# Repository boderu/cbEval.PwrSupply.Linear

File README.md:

# cbEval.PwrSupply.Linear

Evaluation-Board - basierend auf dem modularen Gehäuse von Camdenboss. Stromversorgung mit Linearreglern.

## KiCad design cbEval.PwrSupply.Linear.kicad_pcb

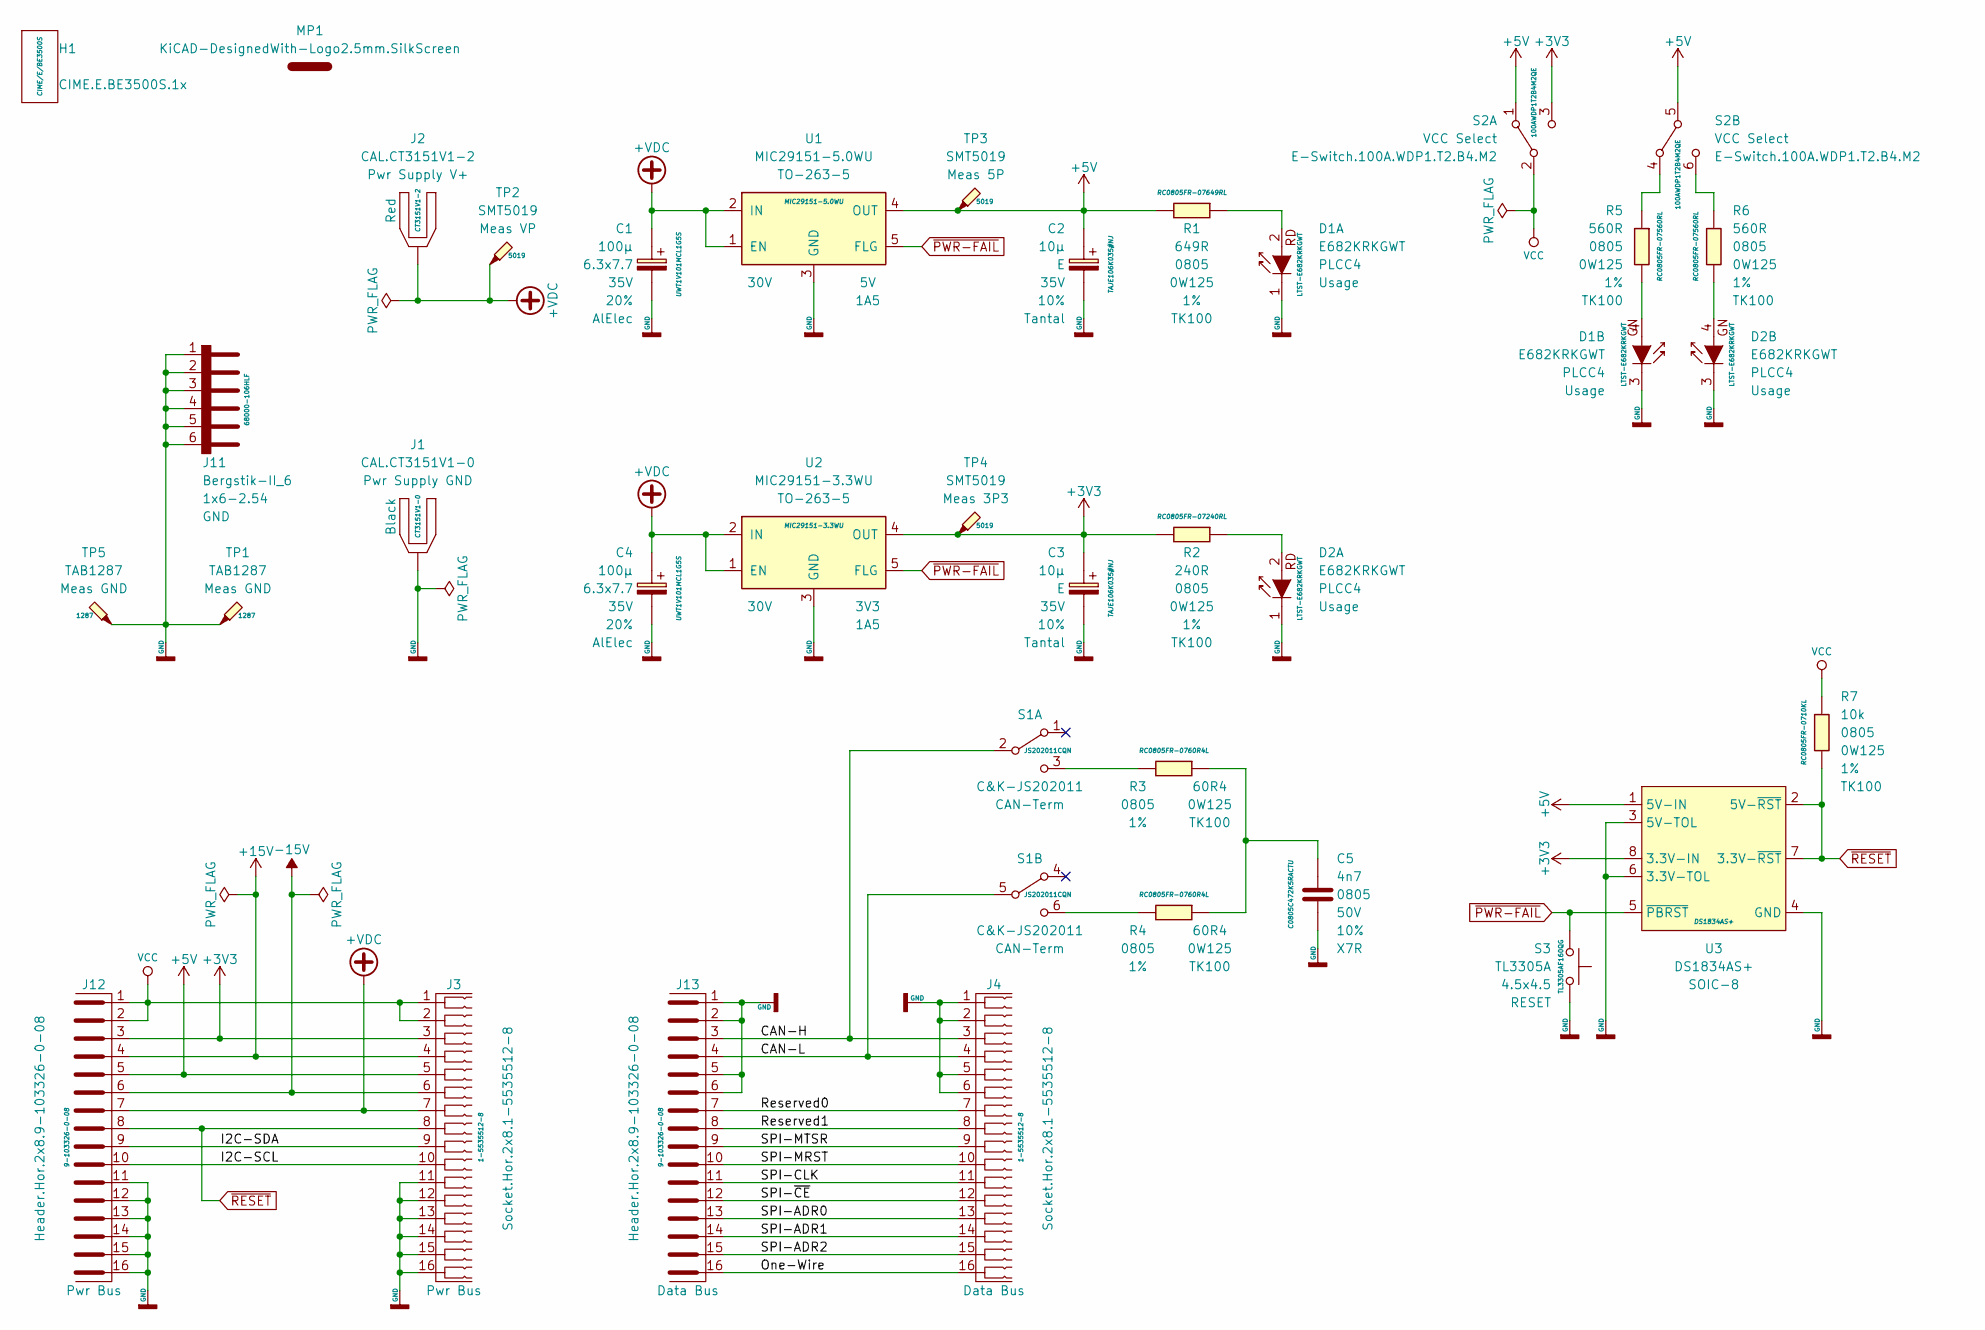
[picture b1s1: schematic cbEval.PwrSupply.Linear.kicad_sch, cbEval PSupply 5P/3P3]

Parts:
C1, C4: 100µ; CP_Elec_6.3x7.7; Voltage 35V; Tolerance 20%
C2, C3: 10µ; CP_EIA-7360-38_Kemet-E; Voltage 35V; Tolerance 10%
C5: 4n7; C_0805_2012Metric; Voltage 50V; Tolerance 10%
D1, D2: E682KRKGWT; LED_Avago_PLCC4_3.2x2.8mm_CW
H1: CIME.E.BE3500S.1x; Camdenboss.CIME.E.BE3500S.1x
J1: CAL.CT3151V1-0; CAL.CT3151V1
J2: CAL.CT3151V1-2; CAL.CT3151V1
J3, J4: Socket.Hor.2x8.1-5535512-8; Socket.Hor.2x5.6-5535512-4
J11: Bergstik-II_6; PinHeader_1x06_P2.54mm_Vertical
J12, J13: Header.Hor.2x8.9-103326-0-08; PinHeader_2x08_P2.54mm_Horizontal
MP1: KiCAD-DesignedWith-Logo2.5mm.SilkScreen; KiCad-Logo2_5mm_SilkScreen
R1: 649R; R_0805_2012Metric; Tolerance 1%
R2: 240R; R_0805_2012Metric; Tolerance 1%
R3, R4: 60R4; R_0805_2012Metric; Tolerance 1%
R5, R6: 560R; R_0805_2012Metric; Tolerance 1%
R7: 10k; R_0805_2012Metric; Tolerance 1%
S1: C&K-JS202011; SW_CuK_JS202011CQN_DPDT_Straight
S2: E-Switch.100A.WDP1.T2.B4.M2; E-Switch.100A.M2.DPDT
S3: TL3305A; SW_SPST_TL3305A
TP1, TP5: TAB1287; TestPoint_Bridge_Pitch5.08mm_Drill1.3mm
TP2, TP3, TP4: SMT5019; TestPoint_Keystone_5019_Minature
U1: MIC29151-5.0WU; TO-263-5_TabPin3; VoltageIn 30V; VoltageOut 5V
U2: MIC29151-3.3WU; TO-263-5_TabPin3; VoltageIn 30V; VoltageOut 3V3
U3: DS1834AS+; SOIC-8_3.9x4.9mm_P1.27mm

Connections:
+3V3: C3.1, J3.3, J12.3, R2.2, S2.3 (C), TP4.1, U2.4 (OUT), U3.8 (3.3V-IN)
+5V: C2.1, J3.5, J12.5, R1.2, S2.1 (A), S2.5 (B), TP3.1, U1.4 (OUT), U3.1 (5V-IN)
+15V: J3.4, J12.4
+VDC: C1.1, C4.1, J2.1, J3.7, J12.7, TP2.1, U1.1 (EN), U1.2 (IN), U2.1 (EN), U2.2 (IN)
-15V: J3.6, J12.6
/CAN-H: J4.3, J13.3, S1.2 (B)
/CAN-L: J4.4, J13.4, S1.5 (B)
/I2C-SCL: J3.10, J12.10
/I2C-SDA: J3.9, J12.9
/One-Wire: J4.16, J13.16
/Reserved0: J4.7, J13.7
/Reserved1: J4.8, J13.8
/SPI-ADR0: J4.13, J13.13
/SPI-ADR1: J4.14, J13.14
/SPI-ADR2: J4.15, J13.15
/SPI-CLK: J4.11, J13.11
/SPI-MRST: J4.10, J13.10
/SPI-MTSR: J4.9, J13.9
/SPI-~CE: J4.12, J13.12
GND: C1.2, C2.2, C3.2, C4.2, C5.2, D1.1 (Rd-C), D1.3 (Gn-C), D2.1 (Rd-C), D2.3 (Gn-C), J1.1, J3.11, J3.12, J3.13, J3.14, J3.15, J3.16, J4.1, J4.2, J4.5, J4.6, J11.1 (A1), J11.2 (A2), J11.3 (A3), J11.4 (A4), J11.5 (A5), J11.6 (A6), J12.11, J12.12, J12.13, J12.14, J12.15, J12.16, J13.1, J13.2, J13.5, J13.6, S3.2, TP1.1, TP5.1, U1.3 (GND), U2.3 (GND), U3.3 (5V-TOL), U3.4 (GND), U3.6 (3.3V-TOL)
unnamed: C5.1, R3.1, R4.1
unnamed: D1.2 (Rd-A), R1.1
unnamed: D1.4 (Gn-A), R5.2
unnamed: D2.2 (Rd-A), R2.1
unnamed: D2.4 (Gn-A), R6.2
unnamed: R3.2, S1.3 (C)
unnamed: R4.2, S1.6 (C)
unnamed: R5.1, S2.4 (A)
unnamed: R6.1, S2.6 (C)
VCC: J3.1, J3.2, J12.1, J12.2, R7.1, S2.2 (B)
~PWR-FAIL: S3.1, U1.5 (FLG), U2.5 (FLG), U3.5 (~PBRST)
~RESET: J3.8, J12.8, R7.2, U3.2 (5V-~RST), U3.7 (3.3V-~RST)

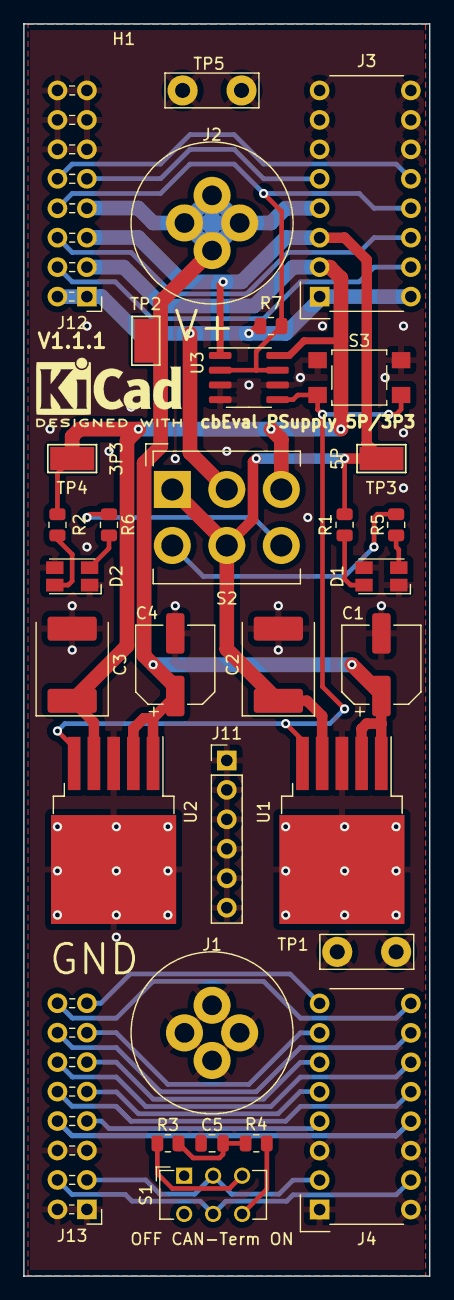
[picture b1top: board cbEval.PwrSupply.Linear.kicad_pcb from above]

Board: 2 copper layers, 35.0 x 108.0 mm, 34 parts (0 on the bottom side), 32 nets.

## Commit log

2021-04-03 Schaltplan und grobe Platzierung fertig
2021-04-03 Ignore-Liste hinzugefügt
2021-04-04 Bus-Leitungen neu belegt
2021-04-04 Bauteil (PinHeader) ausgetauscht
2021-04-06 kleinere Änderungen
2021-04-10 kleinere Korrekturen vor Bauteilbestellung
2021-04-10 Bus-Stecker getauscht
2021-04-11 Properties geändert, Logo aktualisiert
2021-04-18 Layout fertig
2021-06-13 Stromversorgung korrigiert (5P/3P3)
2021-07-18 gespeichert im neuen Format
2021-12-27 Auf das Datenformat der Version 6 umgestellt
2022-01-22 Position von Steckern ausgerückt, SilkScreen von Steckern verändert
2022-02-05 Widerstandswerte zur Ansteuerung derngrünen LEDs auf 560 Ohm verringert. Neue Version 1.1.1
2023-11-08 Update auf KiCAD Version 7
